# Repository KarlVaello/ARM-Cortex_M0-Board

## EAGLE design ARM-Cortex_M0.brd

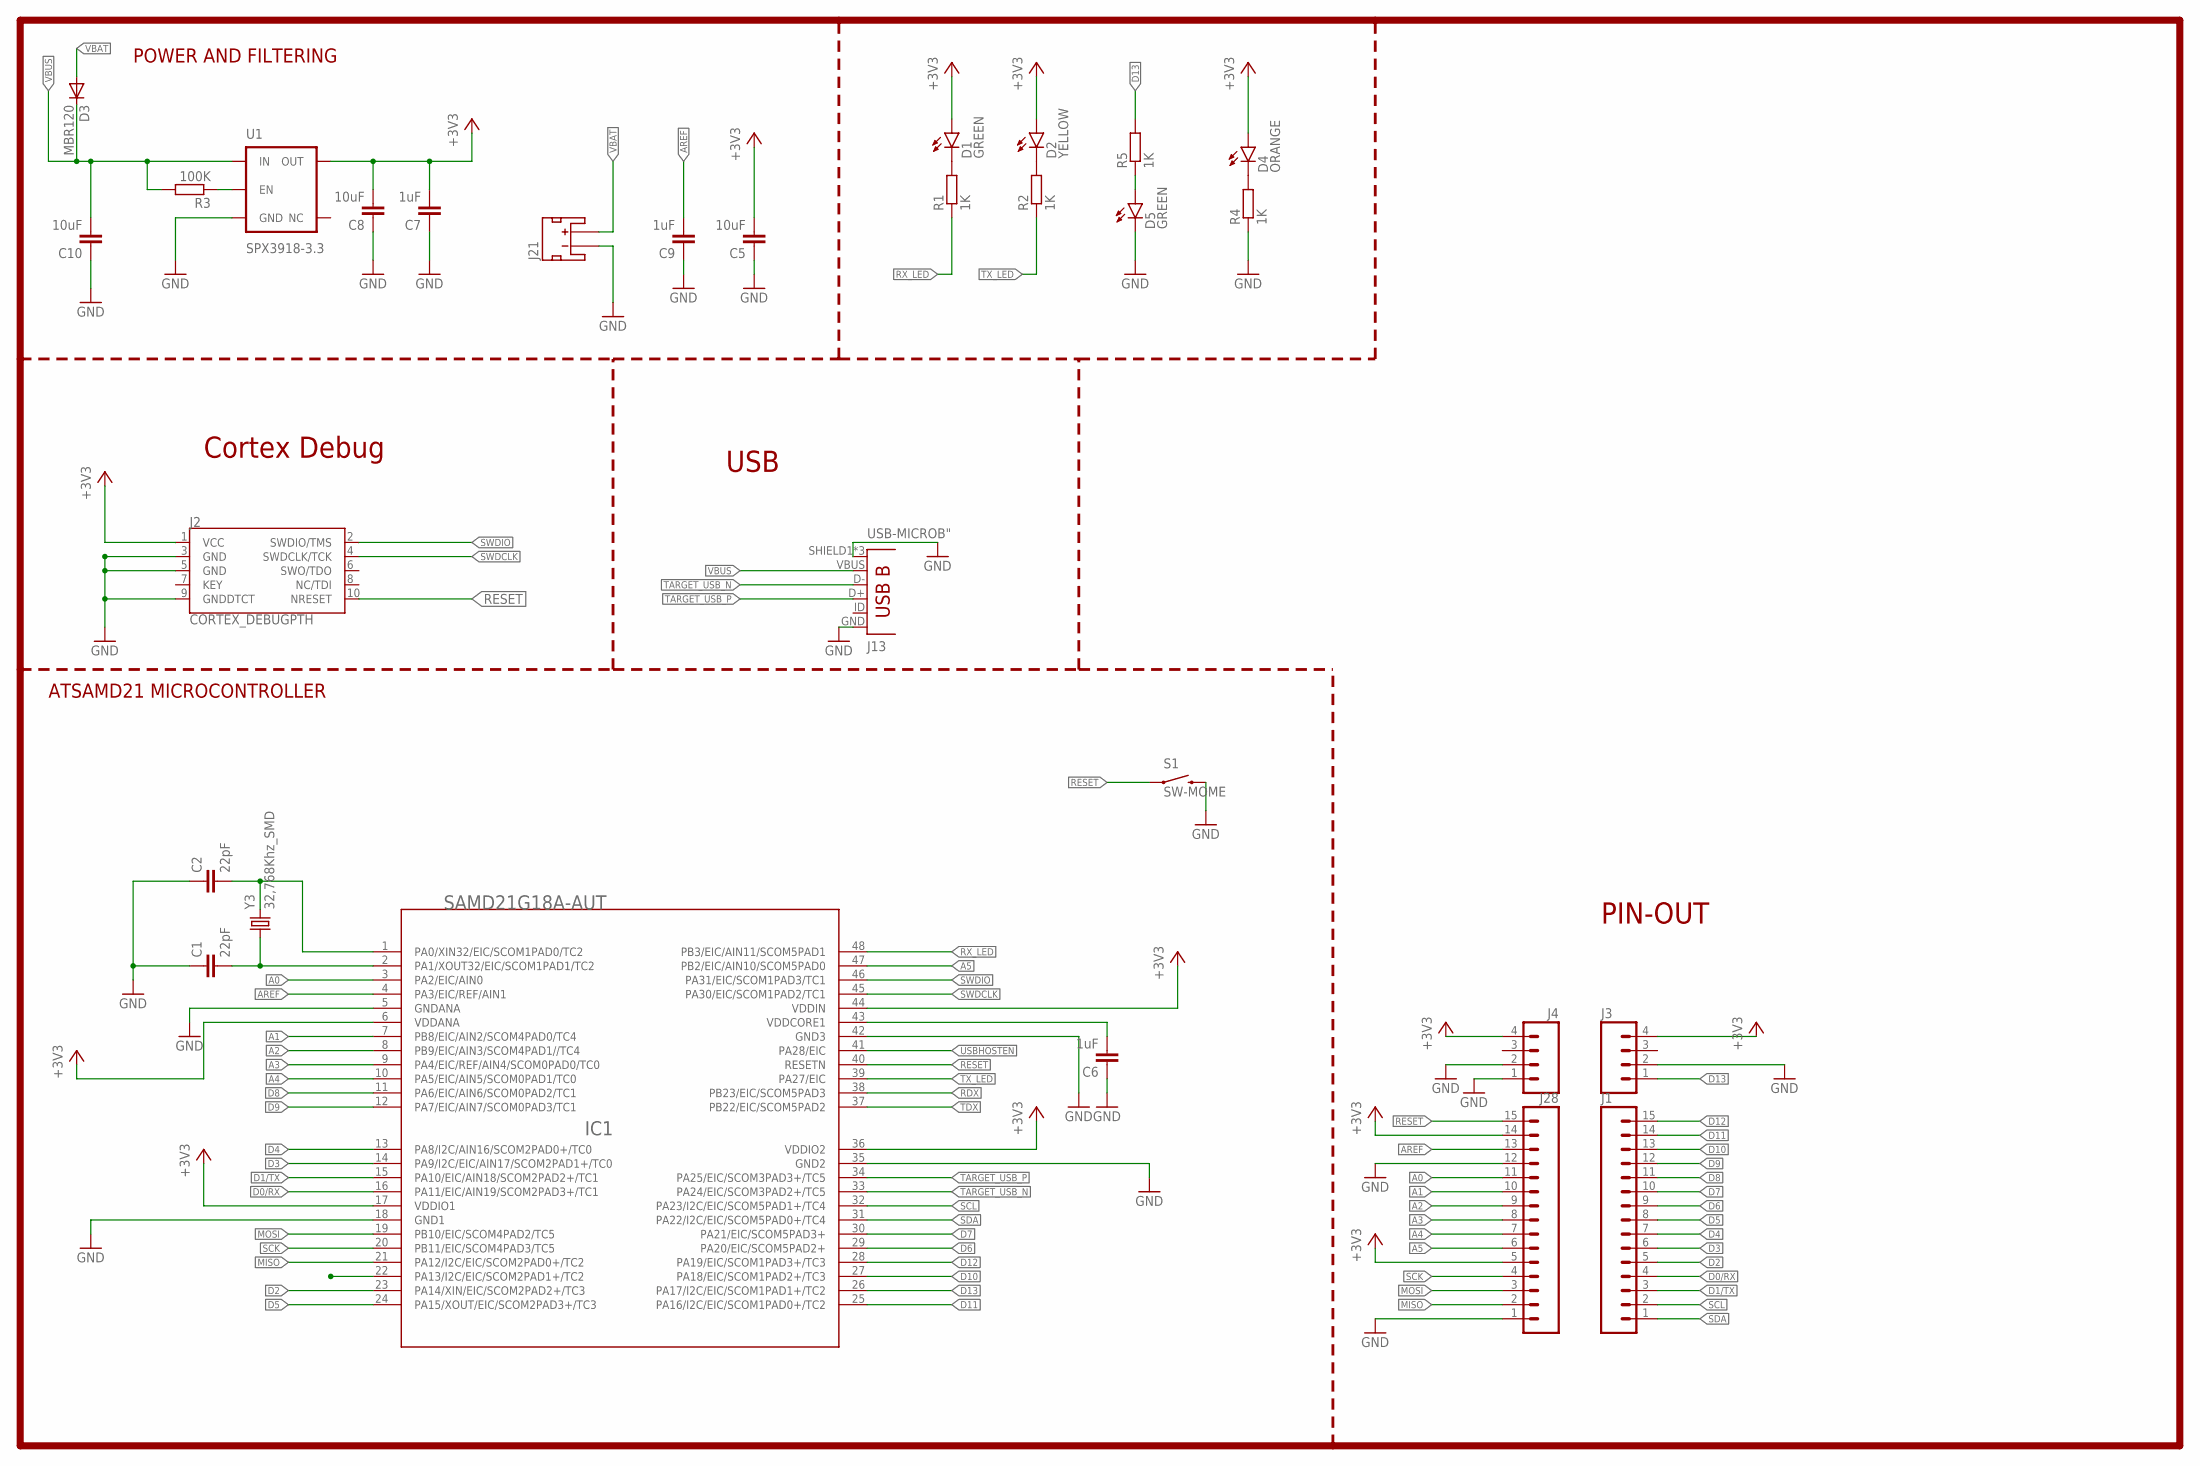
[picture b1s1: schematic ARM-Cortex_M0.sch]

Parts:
C1, C2: 22pF; C0603
C5, C8, C10: 10uF; C0603
C6, C7, C9: 1uF; C0603
D1, D5: GREEN; LED-0603
D2: YELLOW; LED-0603
D3: MBR120; SOD-123_MINI-SMA
D4: ORANGE; LED-0603
IC1: SAMD21G18A-AUT; TQFP48-7X7
J1, J28: M15; 1X15
J2: CORTEX_DEBUGPTH; 2X5-PTH-1.27MM
J3, J4: M04NO_SILK_ALL_ROUND; 1X04_NO_SILK_ALL_ROUND
J13: USB-MICROB"; USB-B-MICRO-SMD_V03
J21: JST_2MM_MALE; JST-2-SMD
R1, R2, R4, R5: 1K; R0603
R3: 100K; R0603
S1: SW-MOME; TACTILE-SWITCH-SMD
U1: SPX3918-3.3; SOT23-5
Y3: 32,768Khz_SMD; CRYSTAL-TXC-7A

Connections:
+3V3: C5.2, C7.2, C8.2, D1.A, D2.A, D4.A, IC1.6 (VDDANA), IC1.17 (VDDIO1), IC1.36 (VDDIO2), IC1.44 (VDDIN), J2.1 (VCC), J3.4, J4.4, J28.5, J28.14, U1.5 (OUT)
A0: IC1.3 (PA2/EIC/AIN0), J28.11
A1: IC1.7 (PB8/EIC/AIN2/SCOM4PAD0/TC4), J28.10
A2: IC1.8 (PB9/EIC/AIN3/SCOM4PAD1//TC4), J28.9
A3: IC1.9 (PA4/EIC/REF/AIN4/SCOM0PAD0/TC0), J28.8
A4: IC1.10 (PA5/EIC/AIN5/SCOM0PAD1/TC0), J28.7
A5: IC1.47 (PB2/EIC/AIN10/SCOM5PAD0), J28.6
AREF: C9.2, IC1.4 (PA3/EIC/REF/AIN1), J28.13
D0/RX: IC1.16 (PA11/EIC/AIN19/SCOM2PAD3+/TC1), J1.4
D1/TX: IC1.15 (PA10/EIC/AIN18/SCOM2PAD2+/TC1), J1.3
D2: IC1.23 (PA14/XIN/EIC/SCOM2PAD2+/TC3), J1.5
D3: IC1.14 (PA9/I2C/EIC/AIN17/SCOM2PAD1+/TC0), J1.6
D4: IC1.13 (PA8/I2C/AIN16/SCOM2PAD0+/TC0), J1.7
D5: IC1.24 (PA15/XOUT/EIC/SCOM2PAD3+/TC3), J1.8
D6: IC1.29 (PA20/EIC/SCOM5PAD2+), J1.9
D7: IC1.30 (PA21/EIC/SCOM5PAD3+), J1.10
D8: IC1.11 (PA6/EIC/AIN6/SCOM0PAD2/TC1), J1.11
D9: IC1.12 (PA7/EIC/AIN7/SCOM0PAD3/TC1), J1.12
D10: IC1.27 (PA18/EIC/SCOM1PAD2+/TC3), J1.13
D11: IC1.25 (PA16/I2C/EIC/SCOM1PAD0+/TC2), J1.14
D12: IC1.28 (PA19/EIC/SCOM1PAD3+/TC3), J1.15
D13: IC1.26 (PA17/I2C/EIC/SCOM1PAD1+/TC2), J3.1, R5.2
GND: C1.1, C2.1, C5.1, C6.1, C7.1, C8.1, C9.1, C10.1, D5.C, IC1.5 (GNDANA), IC1.18 (GND1), IC1.35 (GND2), IC1.42 (GND3), J2.3 (GND), J2.5 (GND), J2.9 (GNDDTCT), J3.2, J4.1, J4.2, J13.GND, J13.SHIELD1 (SHIELD), J13.SHIELD2 (SHIELD), J13.SHIELD3 (SHIELD), J21.1 (-), J28.1, J28.12, R4.1, S1.3 (2), U1.2 (GND)
MISO: IC1.21 (PA12/I2C/EIC/SCOM2PAD0+/TC2), J28.2
MOSI: IC1.19 (PB10/EIC/SCOM4PAD2/TC5), J28.3
unnamed: C1.2, IC1.2 (PA1/XOUT32/EIC/SCOM1PAD1/TC2), Y3.P$1 (1)
unnamed: C2.2, IC1.1 (PA0/XIN32/EIC/SCOM1PAD0/TC2), Y3.P$2 (2)
unnamed: D1.C, R1.2
unnamed: D2.C, R2.2
unnamed: R3.1, U1.3 (EN)
unnamed: C6.2, IC1.43 (VDDCORE1)
unnamed: D4.C, R4.2
unnamed: D5.A, R5.1
RDX: IC1.38 (PB23/EIC/SCOM5PAD3)
RESET: IC1.40 (RESETN), J2.10 (NRESET), J28.15, S1.1
RX_LED: IC1.48 (PB3/EIC/AIN11/SCOM5PAD1), R1.1
SCK: IC1.20 (PB11/EIC/SCOM4PAD3/TC5), J28.4
SCL: IC1.32 (PA23/I2C/EIC/SCOM5PAD1+/TC4), J1.2
SDA: IC1.31 (PA22/I2C/EIC/SCOM5PAD0+/TC4), J1.1
SWDCLK: IC1.45 (PA30/EIC/SCOM1PAD2/TC1), J2.4 (SWDCLK/TCK)
SWDIO: IC1.46 (PA31/EIC/SCOM1PAD3/TC1), J2.2 (SWDIO/TMS)
TARGET_USB_N: IC1.33 (PA24/EIC/SCOM3PAD2+/TC5), J13.D-
TARGET_USB_P: IC1.34 (PA25/EIC/SCOM3PAD3+/TC5), J13.D+
TDX: IC1.37 (PB22/EIC/SCOM5PAD2)
TX_LED: IC1.39 (PA27/EIC), R2.1
USBHOSTEN: IC1.41 (PA28/EIC)
VBAT: D3.A, J21.2 (+)
VBUS: C10.2, D3.C, J13.VBUS, R3.2, U1.1 (IN)

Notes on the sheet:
USB
POWER AND FILTERING
PIN-OUT
Cortex Debug
ATSAMD21 MICROCONTROLLER

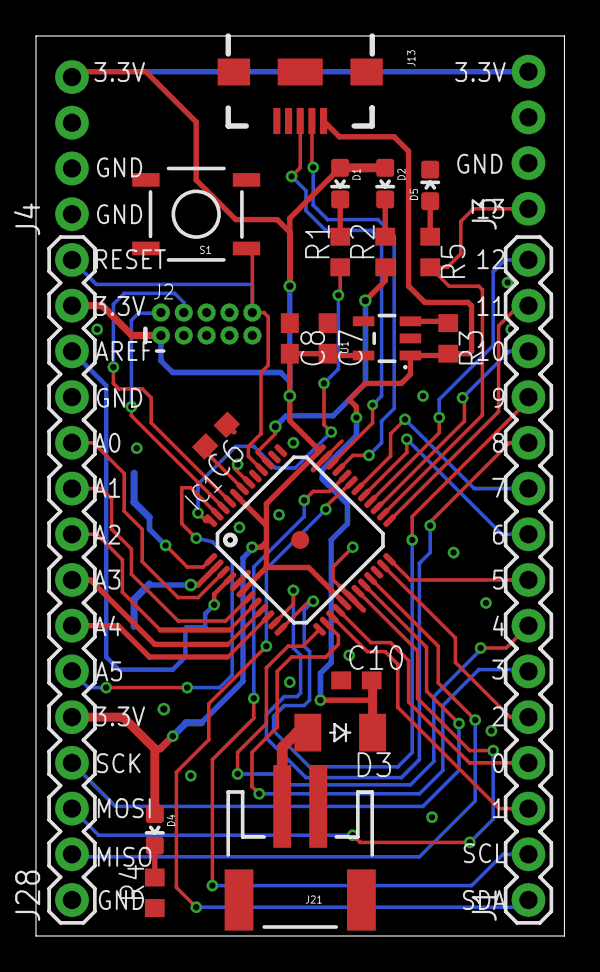
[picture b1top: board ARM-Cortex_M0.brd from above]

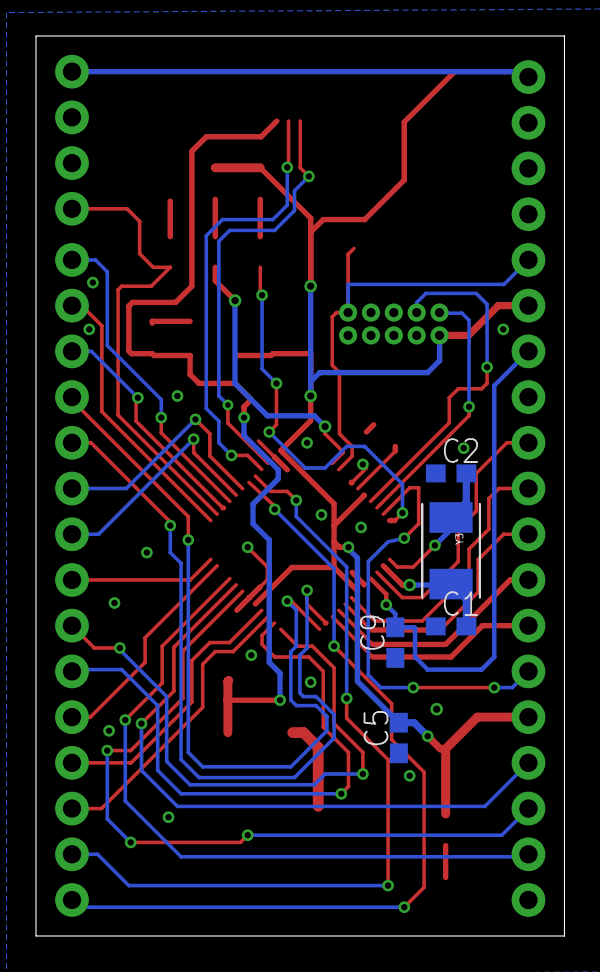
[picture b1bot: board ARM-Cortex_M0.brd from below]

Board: 2 copper layers, 29.4 x 50.0 mm, 29 parts (5 on the bottom side), 45 nets.

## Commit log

2016-10-05 :space_invader: Added .gitattributes & .gitignore files
2016-10-05 Added initial board
    Added initial board
2016-10-05 Addded boot loader info and folder and files were rename
    Addded boot loader info and folder and files was rename
2016-10-06 hardware modifications
    hardware modifications
2016-10-06 hardware
    hardware
2016-10-06 Eagle file version update
    from 7.5.0 to 7.7.0
2016-10-12 Hardaware modification, programing ARM info
    Hardaware modification, programing ARM info
2016-10-12 Added programming info
    Added programming info

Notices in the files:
parts and their libraries:
SparkFun-FreqCtrl: Licensing: Creative Commons ShareAlike 4.0 International - https://creativecommons.org/licenses/by-sa/4.0
